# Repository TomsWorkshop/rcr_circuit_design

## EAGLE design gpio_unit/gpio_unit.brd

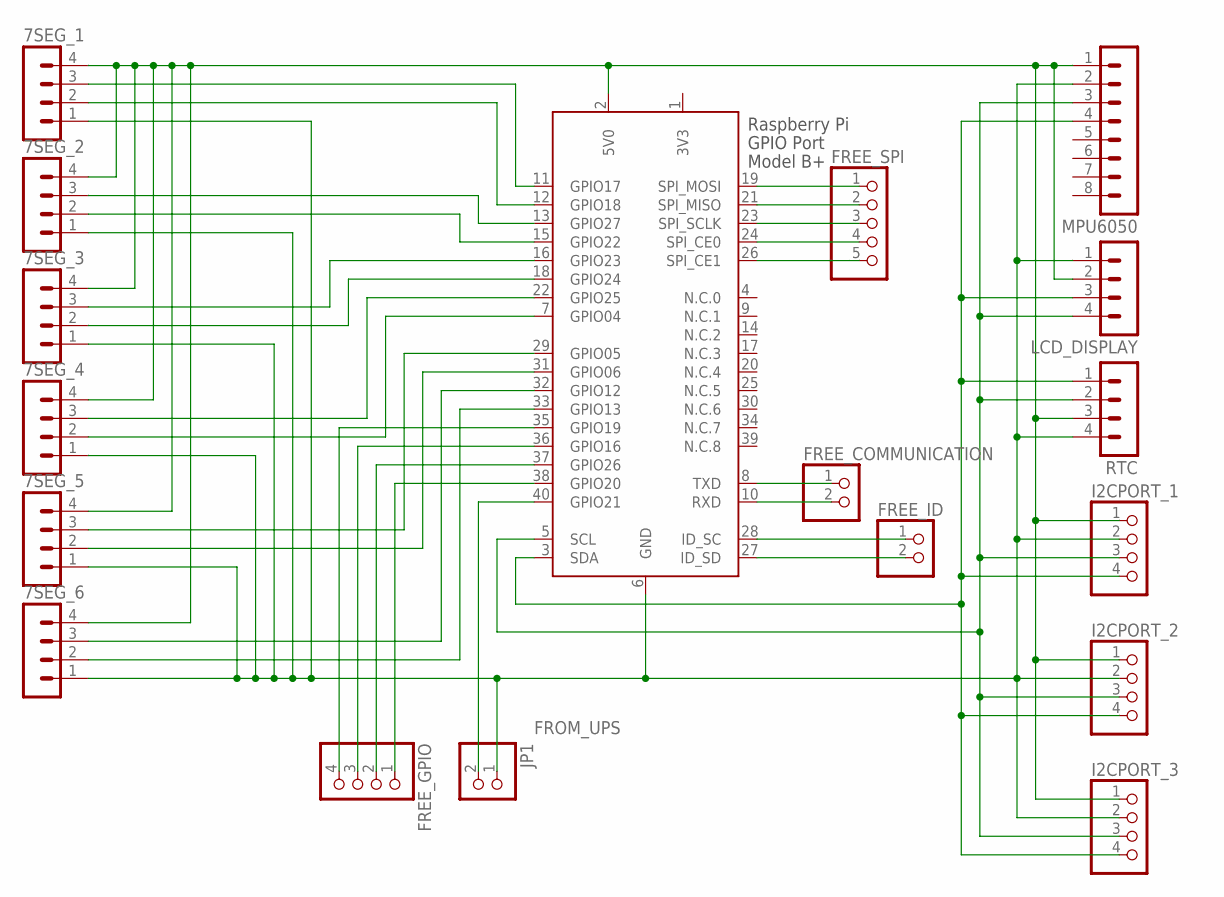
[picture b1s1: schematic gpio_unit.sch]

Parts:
7SEG_1, 7SEG_2, 7SEG_3, 7SEG_4, 7SEG_5, 7SEG_6: MA04-1
FREE_COMMUNICATION: PINHD-1X2/90; 1X02/90
FREE_GPIO: PINHD-1X4/90; 1X04/90
FREE_ID: PINHD-1X2/90; 1X02/90
FREE_SPI: PINHD-1X5/90; 1X05/90
I2CPORT_1, I2CPORT_2, I2CPORT_3: PINHD-1X4; 1X04
JP1: PINHD-1X2; 1X02
LCD_DISPLAY: MA04-1
MPU6050: MA08-1
RTC: MA04-1
X1: RASPI_GPIO_B+_PIN

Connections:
3V3: X1.1 (3V3)
FROM_UPS: JP1.2, X1.40 (GPIO21)
unnamed: 7SEG_1.1, 7SEG_2.1, 7SEG_3.1, 7SEG_4.1, 7SEG_5.1, 7SEG_6.1, I2CPORT_1.2, I2CPORT_2.2, I2CPORT_3.2, JP1.1, LCD_DISPLAY.1, MPU6050.2, RTC.4, X1.6 (GND)
unnamed: 7SEG_1.3, X1.11 (GPIO17)
unnamed: 7SEG_1.2, X1.12 (GPIO18)
unnamed: 7SEG_2.3, X1.13 (GPIO27)
unnamed: I2CPORT_1.3, I2CPORT_2.3, I2CPORT_3.3, LCD_DISPLAY.4, MPU6050.3, RTC.2, X1.5 (SCL)
unnamed: 7SEG_2.2, X1.15 (GPIO22)
unnamed: 7SEG_3.3, X1.16 (GPIO23)
unnamed: 7SEG_3.2, X1.18 (GPIO24)
unnamed: 7SEG_4.3, X1.22 (GPIO25)
unnamed: 7SEG_4.2, X1.7 (GPIO04)
unnamed: 7SEG_5.3, X1.29 (GPIO05)
unnamed: 7SEG_5.2, X1.31 (GPIO06)
unnamed: 7SEG_6.3, X1.32 (GPIO12)
unnamed: 7SEG_6.2, X1.33 (GPIO13)
unnamed: I2CPORT_1.4, I2CPORT_2.4, I2CPORT_3.4, LCD_DISPLAY.3, MPU6050.4, RTC.1, X1.3 (SDA)
unnamed: FREE_SPI.1, X1.19 (SPI_MOSI)
unnamed: FREE_SPI.2, X1.21 (SPI_MISO)
unnamed: FREE_SPI.3, X1.23 (SPI_SCLK)
unnamed: FREE_SPI.4, X1.24 (SPI_CE0)
unnamed: FREE_SPI.5, X1.26 (SPI_CE1)
unnamed: FREE_COMMUNICATION.1, X1.8 (TXD)
unnamed: FREE_COMMUNICATION.2, X1.10 (RXD)
unnamed: FREE_ID.1, X1.28 (ID_SC)
unnamed: FREE_ID.2, X1.27 (ID_SD)
unnamed: FREE_GPIO.4, X1.35 (GPIO19)
unnamed: FREE_GPIO.3, X1.36 (GPIO16)
unnamed: FREE_GPIO.2, X1.37 (GPIO26)
unnamed: FREE_GPIO.1, X1.38 (GPIO20)
VDD: 7SEG_1.4, 7SEG_2.4, 7SEG_3.4, 7SEG_4.4, 7SEG_5.4, 7SEG_6.4, I2CPORT_1.1, I2CPORT_2.1, I2CPORT_3.1, LCD_DISPLAY.2, MPU6050.1, RTC.3, X1.2 (5V0)

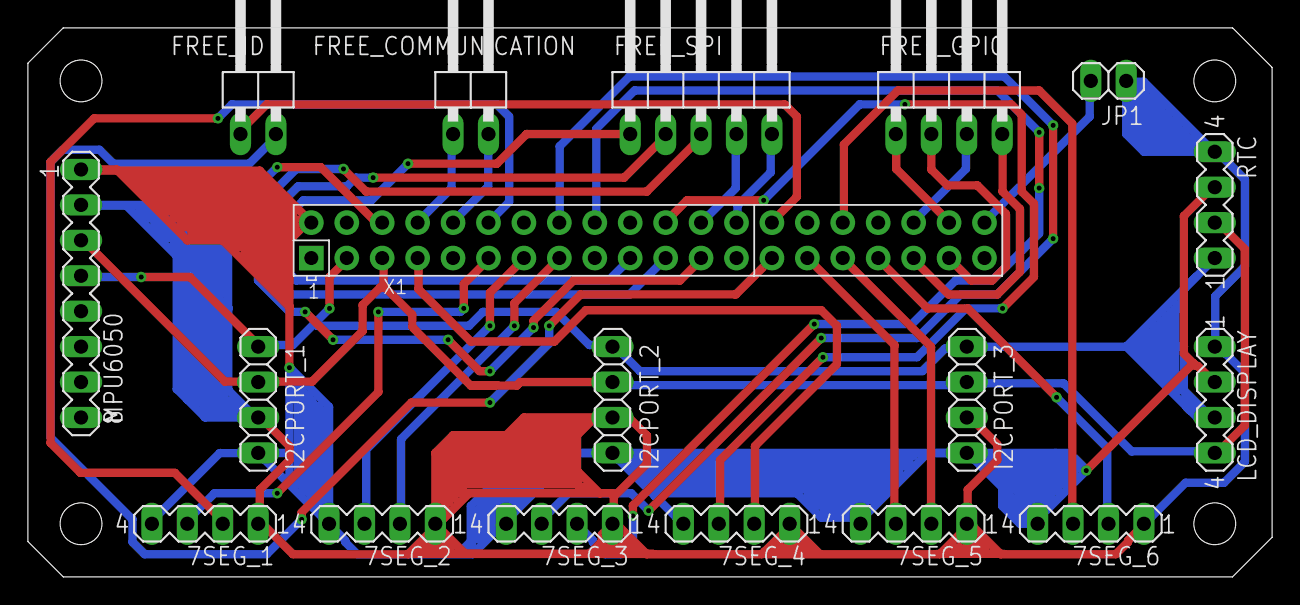
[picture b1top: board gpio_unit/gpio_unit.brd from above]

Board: 2 copper layers, 89.2 x 39.4 mm, 18 parts (0 on the bottom side), 30 nets.

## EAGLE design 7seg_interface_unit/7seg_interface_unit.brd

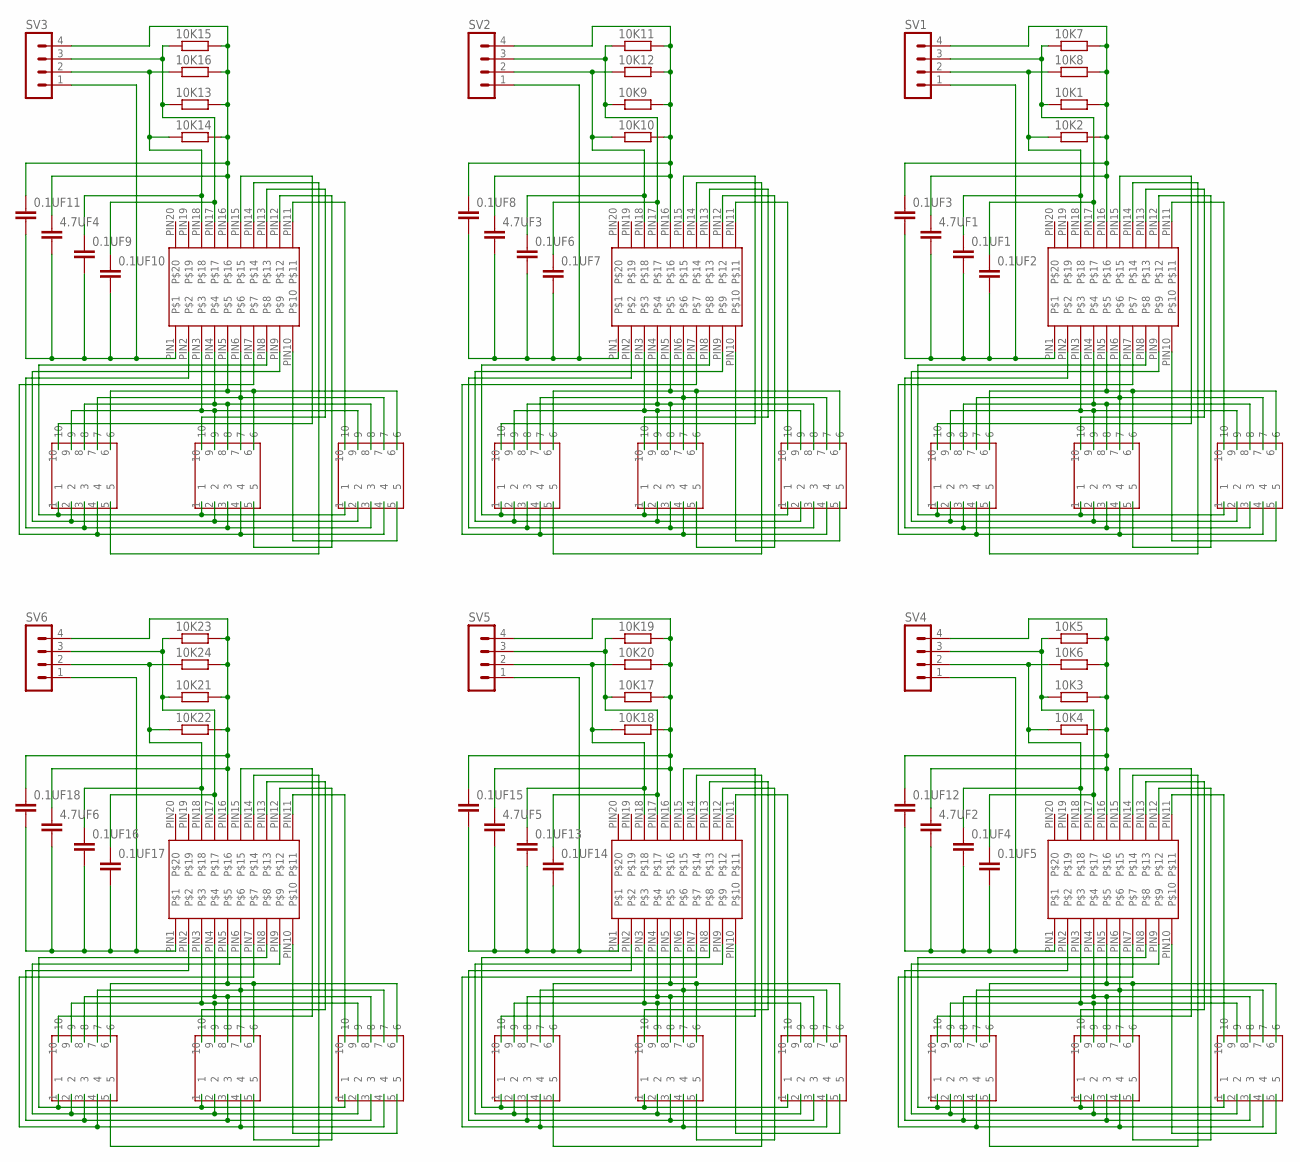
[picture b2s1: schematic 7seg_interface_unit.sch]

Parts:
0.1UF1, 0.1UF2, 0.1UF3, 0.1UF4, 0.1UF5, 0.1UF6, 0.1UF7, 0.1UF8, 0.1UF9, 0.1UF10, 0.1UF11, 0.1UF12, 0.1UF13, 0.1UF14, 0.1UF15, 0.1UF16, 0.1UF17, 0.1UF18: CC1206; C1206
4.7UF1, 4.7UF2, 4.7UF3, 4.7UF4, 4.7UF5, 4.7UF6: CC2012; C2012
10K1, 10K2, 10K3, 10K4, 10K5, 10K6, 10K7, 10K8, 10K9, 10K10, 10K11, 10K12, 10K13, 10K14, 10K15, 10K16, 10K17, 10K18, 10K19, 10K20, 10K21, 10K22, 10K23, 10K24: RR1206; R1206
LED1, LED2, LED3, LED4, LED5, LED6, LED7, LED8, LED9, LED10, LED11, LED12, LED13, LED14, LED15, LED16, LED17, LED18: 7SEG
SV1, SV2, SV3, SV4, SV5, SV6: MA04-1
TM1637-SMD1, TM1637-SMD2, TM1637-SMD3, TM1637-SMD4, TM1637-SMD5, TM1637-SMD6: TM1637

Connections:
unnamed: LED1.1, LED2.1, LED3.1, TM1637-SMD1.PIN8
unnamed: LED1.2, LED2.2, LED3.2, TM1637-SMD1.PIN9
unnamed: LED1.3, LED2.3, LED3.3, TM1637-SMD1.PIN2
unnamed: LED10.1, LED11.1, LED12.1, TM1637-SMD4.PIN8
unnamed: LED10.2, LED11.2, LED12.2, TM1637-SMD4.PIN9
unnamed: LED1.4, LED2.4, LED3.4, TM1637-SMD1.PIN7
unnamed: LED10.3, LED11.3, LED12.3, TM1637-SMD4.PIN2
unnamed: LED1.6, LED2.6, LED3.6, TM1637-SMD1.PIN5
unnamed: LED1.7, LED2.7, LED3.7, TM1637-SMD1.PIN6
unnamed: LED10.4, LED11.4, LED12.4, TM1637-SMD4.PIN7
unnamed: LED1.8, LED2.8, LED3.8, TM1637-SMD1.PIN4
unnamed: LED1.9, LED2.9, LED3.9, TM1637-SMD1.PIN3
unnamed: LED3.5, TM1637-SMD1.PIN10
unnamed: LED3.10, TM1637-SMD1.PIN11
unnamed: LED2.5, TM1637-SMD1.PIN12
unnamed: LED2.10, TM1637-SMD1.PIN13
unnamed: LED1.5, TM1637-SMD1.PIN14
unnamed: LED1.10, TM1637-SMD1.PIN15
unnamed: 0.1UF1.1, 10K2.1, 10K8.1, SV1.2, TM1637-SMD1.PIN18
unnamed: 0.1UF2.1, 10K1.1, 10K7.1, SV1.3, TM1637-SMD1.PIN17
unnamed: 0.1UF3.1, 4.7UF1.1, 10K1.2, 10K2.2, 10K7.2, 10K8.2, SV1.4, TM1637-SMD1.PIN16
unnamed: 0.1UF1.2, 0.1UF2.2, 0.1UF3.2, 4.7UF1.2, SV1.1, TM1637-SMD1.PIN1
unnamed: LED4.1, LED5.1, LED6.1, TM1637-SMD2.PIN8
unnamed: LED4.2, LED5.2, LED6.2, TM1637-SMD2.PIN9
unnamed: LED4.3, LED5.3, LED6.3, TM1637-SMD2.PIN2
unnamed: LED4.4, LED5.4, LED6.4, TM1637-SMD2.PIN7
unnamed: LED4.6, LED5.6, LED6.6, TM1637-SMD2.PIN5
unnamed: LED4.7, LED5.7, LED6.7, TM1637-SMD2.PIN6
unnamed: LED4.8, LED5.8, LED6.8, TM1637-SMD2.PIN4
unnamed: LED4.9, LED5.9, LED6.9, TM1637-SMD2.PIN3
unnamed: LED5.5, TM1637-SMD2.PIN10
unnamed: LED5.10, TM1637-SMD2.PIN11
unnamed: LED4.5, TM1637-SMD2.PIN12
unnamed: LED10.6, LED11.6, LED12.6, TM1637-SMD4.PIN5
unnamed: LED4.10, TM1637-SMD2.PIN13
unnamed: LED6.5, TM1637-SMD2.PIN14
unnamed: LED6.10, TM1637-SMD2.PIN15
unnamed: 0.1UF6.1, 10K10.1, 10K12.1, SV2.2, TM1637-SMD2.PIN18
unnamed: 0.1UF7.1, 10K9.1, 10K11.1, SV2.3, TM1637-SMD2.PIN17
unnamed: 0.1UF8.1, 4.7UF3.1, 10K9.2, 10K10.2, 10K11.2, 10K12.2, SV2.4, TM1637-SMD2.PIN16
unnamed: 0.1UF6.2, 0.1UF7.2, 0.1UF8.2, 4.7UF3.2, SV2.1, TM1637-SMD2.PIN1
unnamed: LED7.1, LED8.1, LED9.1, TM1637-SMD3.PIN8
unnamed: LED7.2, LED8.2, LED9.2, TM1637-SMD3.PIN9
unnamed: LED10.7, LED11.7, LED12.7, TM1637-SMD4.PIN6
unnamed: LED7.3, LED8.3, LED9.3, TM1637-SMD3.PIN2
unnamed: LED7.4, LED8.4, LED9.4, TM1637-SMD3.PIN7
unnamed: LED7.6, LED8.6, LED9.6, TM1637-SMD3.PIN5
unnamed: LED7.7, LED8.7, LED9.7, TM1637-SMD3.PIN6
unnamed: LED7.8, LED8.8, LED9.8, TM1637-SMD3.PIN4
unnamed: LED7.9, LED8.9, LED9.9, TM1637-SMD3.PIN3
unnamed: LED8.5, TM1637-SMD3.PIN10
unnamed: LED8.10, TM1637-SMD3.PIN11
unnamed: LED7.5, TM1637-SMD3.PIN12
unnamed: LED7.10, TM1637-SMD3.PIN13
unnamed: LED9.5, TM1637-SMD3.PIN14
unnamed: LED9.10, TM1637-SMD3.PIN15
unnamed: 0.1UF9.1, 10K14.1, 10K16.1, SV3.2, TM1637-SMD3.PIN18
unnamed: 0.1UF10.1, 10K13.1, 10K15.1, SV3.3, TM1637-SMD3.PIN17
unnamed: 0.1UF11.1, 4.7UF4.1, 10K13.2, 10K14.2, 10K15.2, 10K16.2, SV3.4, TM1637-SMD3.PIN16
unnamed: 0.1UF9.2, 0.1UF10.2, 0.1UF11.2, 4.7UF4.2, SV3.1, TM1637-SMD3.PIN1
unnamed: LED10.8, LED11.8, LED12.8, TM1637-SMD4.PIN4
unnamed: LED10.9, LED11.9, LED12.9, TM1637-SMD4.PIN3
unnamed: LED11.5, TM1637-SMD4.PIN10
unnamed: LED11.10, TM1637-SMD4.PIN11
unnamed: LED10.5, TM1637-SMD4.PIN12
unnamed: LED10.10, TM1637-SMD4.PIN13
unnamed: LED12.5, TM1637-SMD4.PIN14
unnamed: LED12.10, TM1637-SMD4.PIN15
unnamed: 0.1UF4.1, 10K4.1, 10K6.1, SV4.2, TM1637-SMD4.PIN18
unnamed: 0.1UF5.1, 10K3.1, 10K5.1, SV4.3, TM1637-SMD4.PIN17
unnamed: 0.1UF12.1, 4.7UF2.1, 10K3.2, 10K4.2, 10K5.2, 10K6.2, SV4.4, TM1637-SMD4.PIN16
unnamed: 0.1UF4.2, 0.1UF5.2, 0.1UF12.2, 4.7UF2.2, SV4.1, TM1637-SMD4.PIN1
unnamed: LED13.1, LED14.1, LED15.1, TM1637-SMD5.PIN8
unnamed: LED13.2, LED14.2, LED15.2, TM1637-SMD5.PIN9
unnamed: LED13.3, LED14.3, LED15.3, TM1637-SMD5.PIN2
unnamed: LED13.4, LED14.4, LED15.4, TM1637-SMD5.PIN7
unnamed: LED13.6, LED14.6, LED15.6, TM1637-SMD5.PIN5
unnamed: LED13.7, LED14.7, LED15.7, TM1637-SMD5.PIN6
unnamed: LED13.8, LED14.8, LED15.8, TM1637-SMD5.PIN4
unnamed: LED13.9, LED14.9, LED15.9, TM1637-SMD5.PIN3
unnamed: LED14.5, TM1637-SMD5.PIN10
unnamed: LED14.10, TM1637-SMD5.PIN11
unnamed: LED13.5, TM1637-SMD5.PIN12
unnamed: LED13.10, TM1637-SMD5.PIN13
unnamed: LED15.5, TM1637-SMD5.PIN14
unnamed: LED15.10, TM1637-SMD5.PIN15
unnamed: 0.1UF13.1, 10K18.1, 10K20.1, SV5.2, TM1637-SMD5.PIN18
unnamed: 0.1UF14.1, 10K17.1, 10K19.1, SV5.3, TM1637-SMD5.PIN17
unnamed: 0.1UF15.1, 4.7UF5.1, 10K17.2, 10K18.2, 10K19.2, 10K20.2, SV5.4, TM1637-SMD5.PIN16
unnamed: 0.1UF13.2, 0.1UF14.2, 0.1UF15.2, 4.7UF5.2, SV5.1, TM1637-SMD5.PIN1
unnamed: LED16.1, LED17.1, LED18.1, TM1637-SMD6.PIN8
unnamed: LED16.2, LED17.2, LED18.2, TM1637-SMD6.PIN9
unnamed: LED16.3, LED17.3, LED18.3, TM1637-SMD6.PIN2
unnamed: LED16.4, LED17.4, LED18.4, TM1637-SMD6.PIN7
unnamed: LED16.6, LED17.6, LED18.6, TM1637-SMD6.PIN5
unnamed: LED16.7, LED17.7, LED18.7, TM1637-SMD6.PIN6
unnamed: LED16.8, LED17.8, LED18.8, TM1637-SMD6.PIN4
unnamed: LED16.9, LED17.9, LED18.9, TM1637-SMD6.PIN3
unnamed: LED17.5, TM1637-SMD6.PIN10
unnamed: LED17.10, TM1637-SMD6.PIN11
unnamed: LED16.5, TM1637-SMD6.PIN12
unnamed: LED16.10, TM1637-SMD6.PIN13
unnamed: LED18.5, TM1637-SMD6.PIN14
unnamed: LED18.10, TM1637-SMD6.PIN15
unnamed: 0.1UF16.1, 10K22.1, 10K24.1, SV6.2, TM1637-SMD6.PIN18
unnamed: 0.1UF17.1, 10K21.1, 10K23.1, SV6.3, TM1637-SMD6.PIN17
unnamed: 0.1UF18.1, 4.7UF6.1, 10K21.2, 10K22.2, 10K23.2, 10K24.2, SV6.4, TM1637-SMD6.PIN16
unnamed: 0.1UF16.2, 0.1UF17.2, 0.1UF18.2, 4.7UF6.2, SV6.1, TM1637-SMD6.PIN1

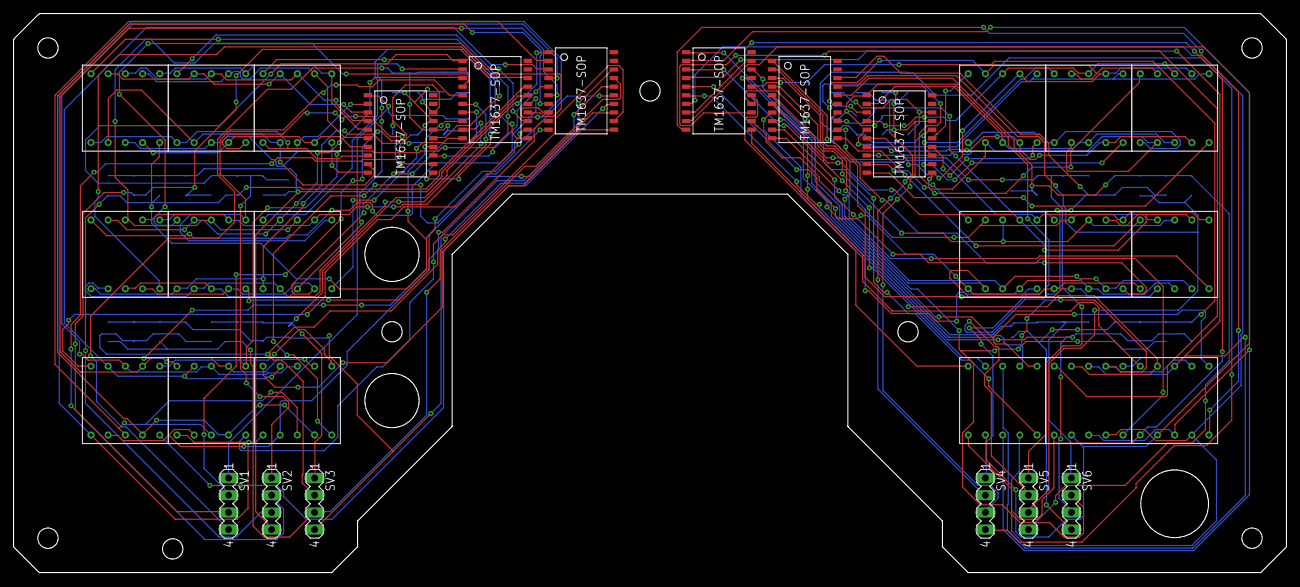
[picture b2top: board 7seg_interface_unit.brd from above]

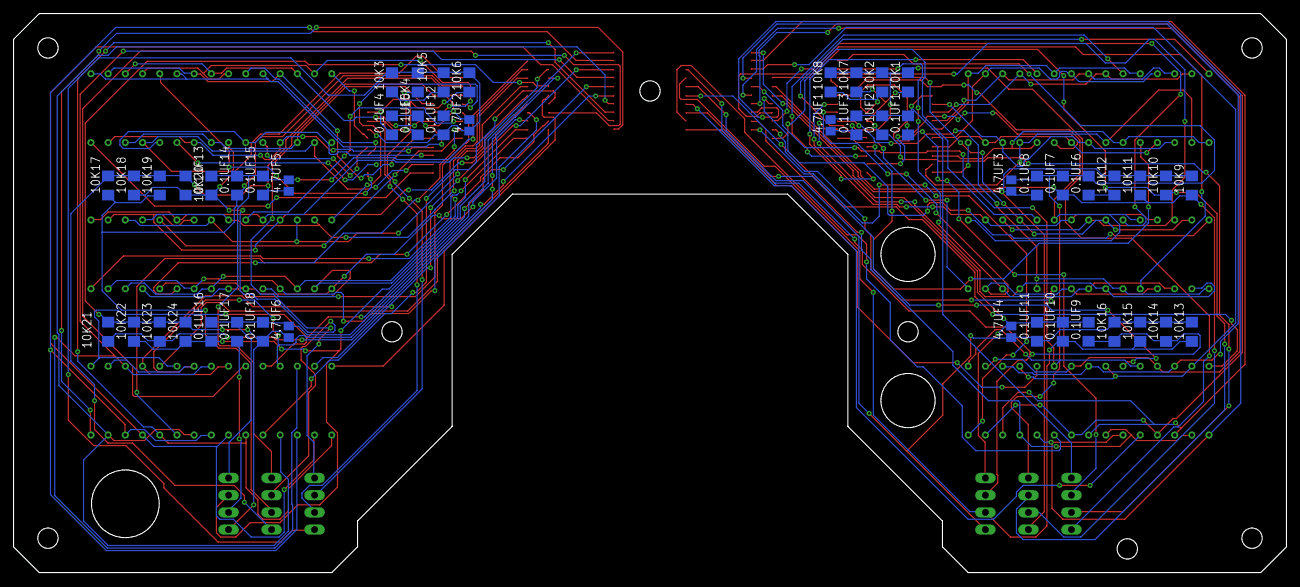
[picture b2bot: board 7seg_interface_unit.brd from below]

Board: 2 copper layers, 187.8 x 82.5 mm, 78 parts (48 on the bottom side), 108 nets.

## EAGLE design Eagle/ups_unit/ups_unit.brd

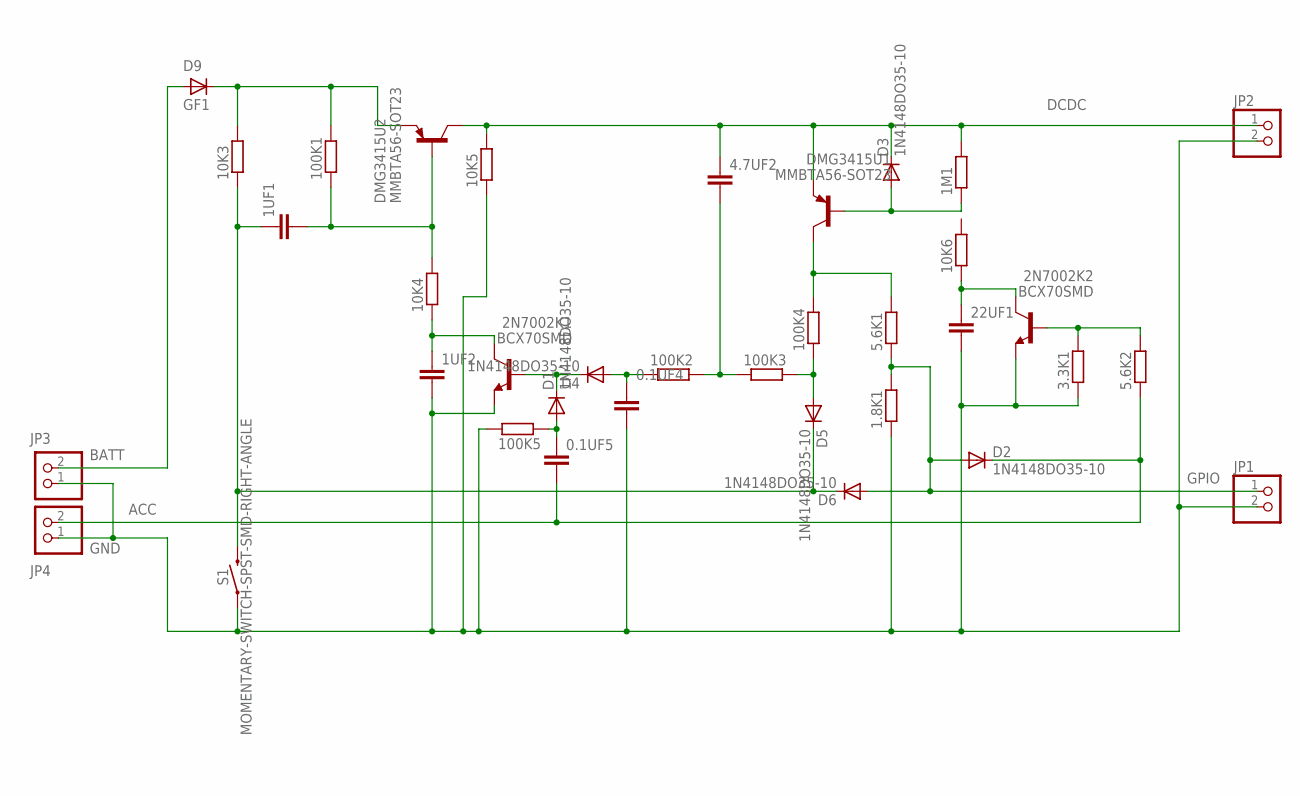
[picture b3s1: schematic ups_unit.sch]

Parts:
0.1UF4, 0.1UF5: CC1206; C1206
1.8K1, 1M1, 3.3K1, 5.6K1, 5.6K2, 10K3, 10K4, 10K5, 10K6, 100K1, 100K2, 100K3, 100K4, 100K5: RR1206; R1206
1UF1, 1UF2: CC0603; C0603
2N7002K1, 2N7002K2: BCX70SMD; SOT23
4.7UF2: CC2012; C2012
22UF1: C; C0805
D1, D2, D3, D4, D5, D6: 1N4148DO35-10; DO35-10
D9: GF1; SMA-DO214AC
DMG3415U1, DMG3415U2: MMBTA56-SOT23; SOT23
JP1, JP2, JP3, JP4: PINHD-1X2; 1X02
S1: MOMENTARY-SWITCH-SPST-SMD-RIGHT-ANGLE; TACTILE_SWITCH_SMD_RIGHT_ANGLE

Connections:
ACC: 0.1UF5.2, 5.6K2.1, D2.C, JP4.2
BATT: D9.A, JP3.2
DCDC: 1M1.2, 4.7UF2.1, 10K5.2, D3.C, DMG3415U1.2 (E), DMG3415U2.3 (C), JP2.1
GND: 0.1UF4.2, 1.8K1.1, 1UF2.2, 2N7002K1.2 (E), 2N7002K2.2 (E), 3.3K1.1, 10K5.1, 22UF1.2, 100K5.2, JP1.2, JP2.2, JP3.1, JP4.1, S1.1
GPIO: 1.8K1.2, 5.6K1.1, D2.A, D6.A, JP1.1
unnamed: 10K3.2, 100K1.2, D9.K (C), DMG3415U2.2 (E)
unnamed: 1UF1.1, 10K3.1, D5.C, D6.C, S1.2
unnamed: 1UF1.2, 10K4.2, 100K1.1, DMG3415U2.1 (B)
unnamed: 1UF2.1, 2N7002K1.3 (C), 10K4.1
unnamed: 2N7002K1.1 (B), D1.C, D4.C
unnamed: 0.1UF4.1, 100K2.1, D4.A
unnamed: 4.7UF2.2, 100K2.2, 100K3.1
unnamed: 5.6K1.2, 100K4.2, DMG3415U1.3 (C)
unnamed: 100K3.2, 100K4.1, D5.A
unnamed: 0.1UF5.1, 100K5.1, D1.A
unnamed: 1M1.1, D3.A, DMG3415U1.1 (B)
unnamed: 2N7002K2.3 (C), 10K6.1, 22UF1.1
unnamed: 2N7002K2.1 (B), 3.3K1.2, 5.6K2.2

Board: 2 copper layers, 36 parts (32 on the bottom side), 18 nets, no tracks yet.

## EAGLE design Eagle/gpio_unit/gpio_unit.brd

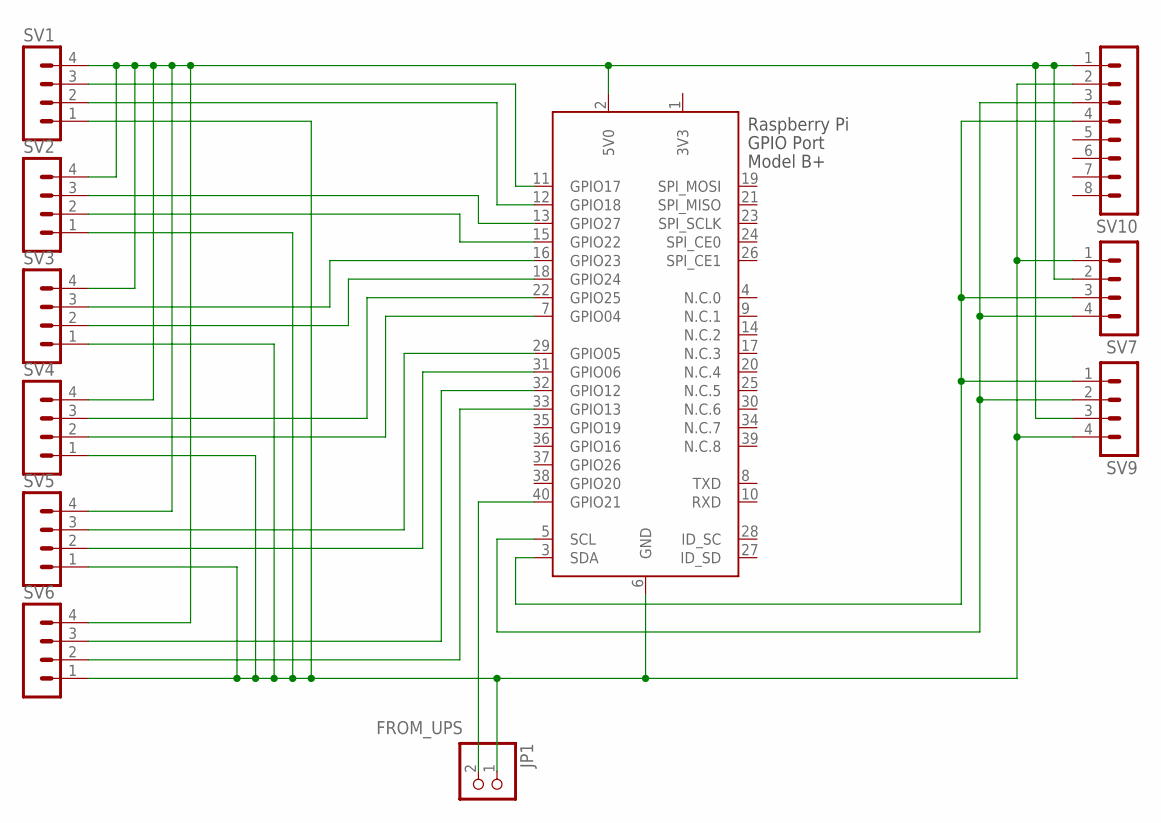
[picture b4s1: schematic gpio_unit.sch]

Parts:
JP1: PINHD-1X2; 1X02
SV1, SV2, SV3, SV4, SV5, SV6, SV7, SV9: MA04-1
SV10: MA08-1
X1: RASPI_GPIO_B+_PIN

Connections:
3V3: X1.1 (3V3)
FROM_UPS: JP1.2, X1.40 (GPIO21)
unnamed: JP1.1, SV1.1, SV2.1, SV3.1, SV4.1, SV5.1, SV6.1, SV7.1, SV9.4, SV10.2, X1.6 (GND)
unnamed: SV1.3, X1.11 (GPIO17)
unnamed: SV1.2, X1.12 (GPIO18)
unnamed: SV2.3, X1.13 (GPIO27)
unnamed: SV7.4, SV9.2, SV10.3, X1.5 (SCL)
unnamed: SV2.2, X1.15 (GPIO22)
unnamed: SV3.3, X1.16 (GPIO23)
unnamed: SV3.2, X1.18 (GPIO24)
unnamed: SV4.3, X1.22 (GPIO25)
unnamed: SV4.2, X1.7 (GPIO04)
unnamed: SV5.3, X1.29 (GPIO05)
unnamed: SV5.2, X1.31 (GPIO06)
unnamed: SV6.3, X1.32 (GPIO12)
unnamed: SV6.2, X1.33 (GPIO13)
unnamed: SV7.3, SV9.1, SV10.4, X1.3 (SDA)
VDD: SV1.4, SV2.4, SV3.4, SV4.4, SV5.4, SV6.4, SV7.2, SV9.3, SV10.1, X1.2 (5V0)

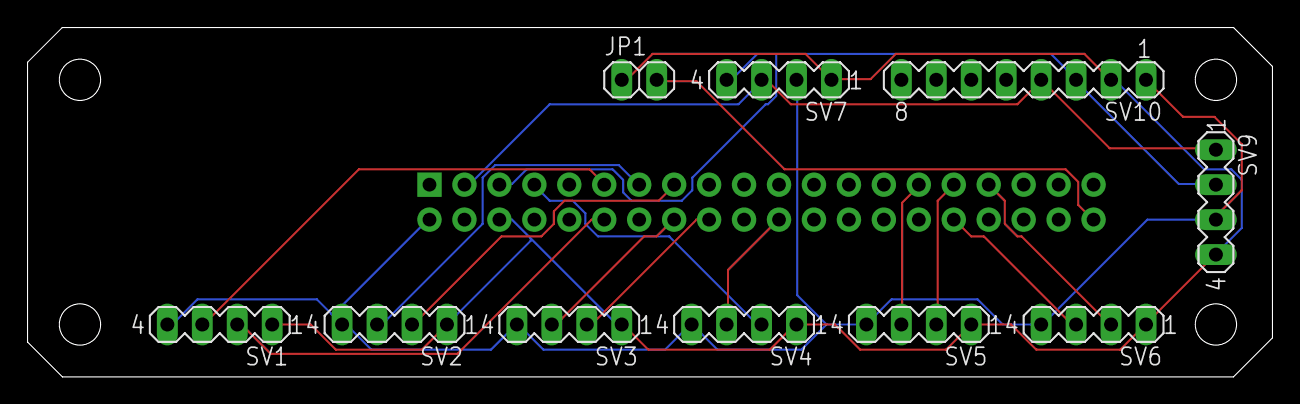
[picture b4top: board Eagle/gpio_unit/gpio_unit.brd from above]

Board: 2 copper layers, 90.5 x 25.4 mm, 11 parts (1 on the bottom side), 17 nets.

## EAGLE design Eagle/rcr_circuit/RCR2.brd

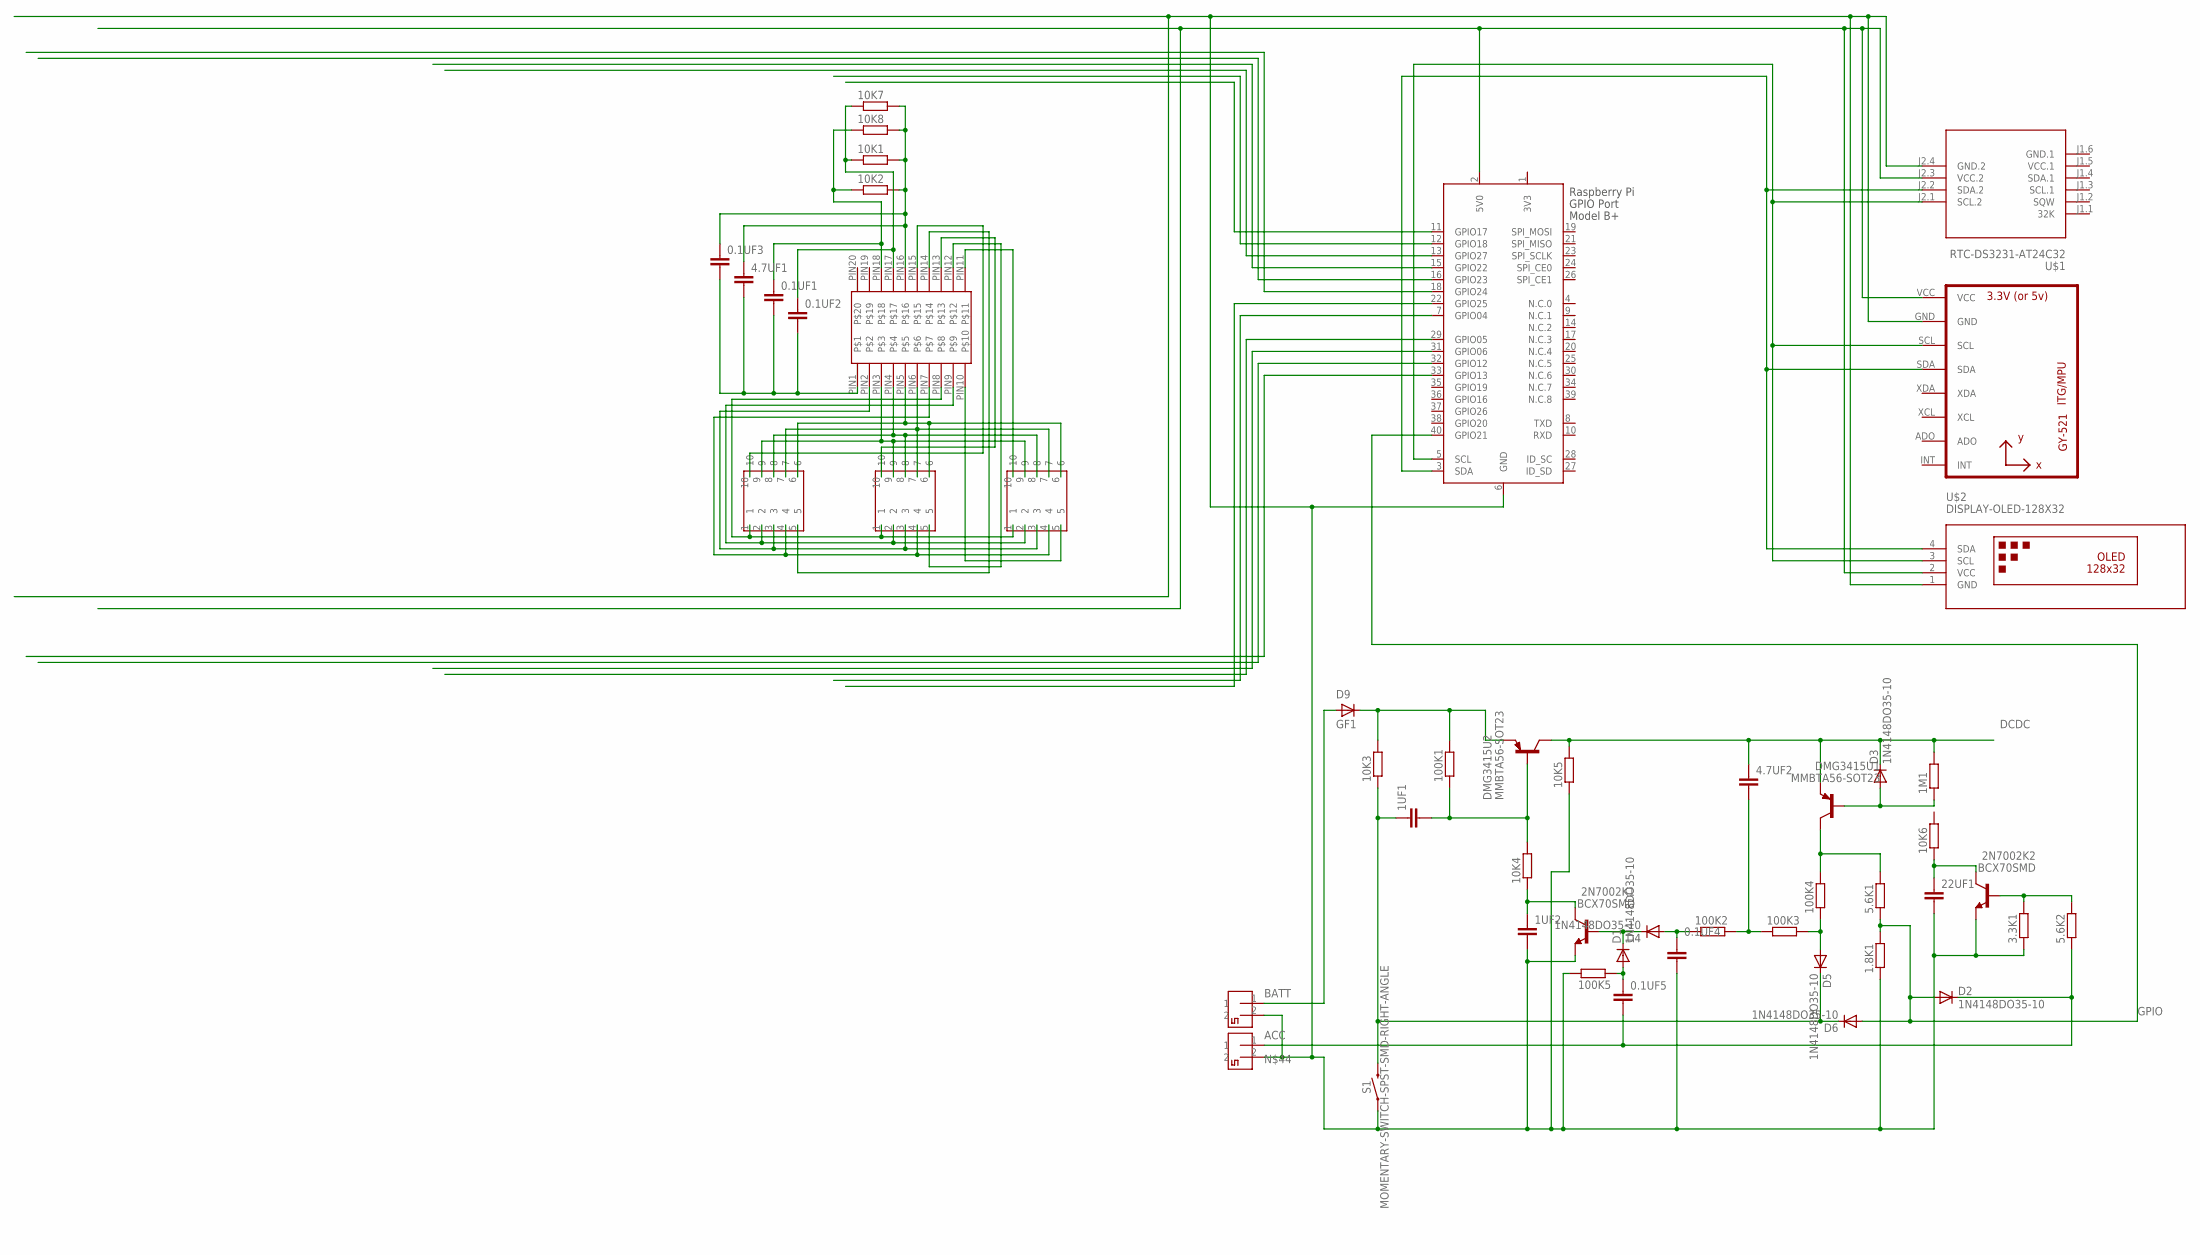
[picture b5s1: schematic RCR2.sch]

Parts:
0.1UF1, 0.1UF2, 0.1UF3, 0.1UF4, 0.1UF5: CC1206; C1206
1.8K1, 1M1, 3.3K1, 5.6K1, 5.6K2, 10K1, 10K2, 10K3, 10K4, 10K5, 10K6, 10K7, 10K8, 100K1, 100K2, 100K3, 100K4, 100K5: RR1206; R1206
1UF1, 1UF2: CC0603; C0603
2N7002K1, 2N7002K2: BCX70SMD; SOT23
4.7UF1, 4.7UF2: CC2012; C2012
22UF1: C; C0805
CONNECTOR2, CONNECTOR3: 2PIN
D1, D2, D3, D4, D5, D6: 1N4148DO35-10; DO35-10
D9: GF1; SMA-DO214AC
DMG3415U1, DMG3415U2: MMBTA56-SOT23; SOT23
LED1, LED2, LED3: 7SEG
S1: MOMENTARY-SWITCH-SPST-SMD-RIGHT-ANGLE; TACTILE_SWITCH_SMD_RIGHT_ANGLE
TM1637-SMD1: TM1637
U1: GY-521MPU6050; GY-521
U$1: RTC-DS3231-AT24C32
U$2: DISPLAY-OLED-128X32
X1: RASPI_GPIO_B+_PIN

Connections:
3V3: X1.1 (3V3)
ACC: 0.1UF5.2, 5.6K2.1, CONNECTOR2.1, D2.C
BATT: CONNECTOR3.1, D9.A
DCDC: 1M1.2, 4.7UF2.1, 10K5.2, D3.C, DMG3415U1.2 (E), DMG3415U2.3 (C)
GND.1: U$1.J1.6 (GND.1)
GPIO: 1.8K1.2, 5.6K1.1, D2.A, D6.A, X1.40 (GPIO21)
unnamed: LED1.1, LED2.1, LED3.1, TM1637-SMD1.PIN8
unnamed: LED1.2, LED2.2, LED3.2, TM1637-SMD1.PIN9
unnamed: LED1.3, LED2.3, LED3.3, TM1637-SMD1.PIN2
unnamed: LED1.4, LED2.4, LED3.4, TM1637-SMD1.PIN7
unnamed: LED1.6, LED2.6, LED3.6, TM1637-SMD1.PIN5
unnamed: LED1.7, LED2.7, LED3.7, TM1637-SMD1.PIN6
unnamed: LED1.8, LED2.8, LED3.8, TM1637-SMD1.PIN4
unnamed: LED1.9, LED2.9, LED3.9, TM1637-SMD1.PIN3
unnamed: LED3.5, TM1637-SMD1.PIN10
unnamed: LED3.10, TM1637-SMD1.PIN11
unnamed: LED2.5, TM1637-SMD1.PIN12
unnamed: LED2.10, TM1637-SMD1.PIN13
unnamed: LED1.5, TM1637-SMD1.PIN14
unnamed: LED1.10, TM1637-SMD1.PIN15
unnamed: 0.1UF1.1, 10K2.1, 10K8.1, TM1637-SMD1.PIN18
unnamed: 0.1UF2.1, 10K1.1, 10K7.1, TM1637-SMD1.PIN17
unnamed: 0.1UF3.1, 4.7UF1.1, 10K1.2, 10K2.2, 10K7.2, 10K8.2, TM1637-SMD1.PIN16
unnamed: 0.1UF1.2, 0.1UF2.2, 0.1UF3.2, 4.7UF1.2, TM1637-SMD1.PIN1
unnamed: U1.SCL, U$1.J2.1 (SCL.2), U$2.3 (SCL), X1.5 (SCL)
unnamed: 0.1UF4.2, 1.8K1.1, 1UF2.2, 2N7002K1.2 (E), 2N7002K2.2 (E), 3.3K1.1, 10K5.1, 22UF1.2, 100K5.2, CONNECTOR2.2, CONNECTOR3.2, S1.1, U1.GND, U$1.J2.4 (GND.2), U$2.1 (GND), X1.6 (GND)
unnamed: U1.SDA, U$1.J2.2 (SDA.2), U$2.4 (SDA), X1.3 (SDA)
unnamed: 10K3.2, 100K1.2, D9.K (C), DMG3415U2.2 (E)
unnamed: 1UF1.1, 10K3.1, D5.C, D6.C, S1.2
unnamed: 1UF1.2, 10K4.2, 100K1.1, DMG3415U2.1 (B)
unnamed: 1UF2.1, 2N7002K1.3 (C), 10K4.1
unnamed: 2N7002K1.1 (B), D1.C, D4.C
unnamed: 0.1UF4.1, 100K2.1, D4.A
unnamed: 4.7UF2.2, 100K2.2, 100K3.1
unnamed: 5.6K1.2, 100K4.2, DMG3415U1.3 (C)
unnamed: 100K3.2, 100K4.1, D5.A
unnamed: 0.1UF5.1, 100K5.1, D1.A
unnamed: 1M1.1, D3.A, DMG3415U1.1 (B)
unnamed: 2N7002K2.3 (C), 10K6.1, 22UF1.1
unnamed: 2N7002K2.1 (B), 3.3K1.2, 5.6K2.2
VCC.1: U$1.J1.5 (VCC.1)
VDD: U1.VCC, U$1.J2.3 (VCC.2), U$2.2 (VCC), X1.2 (5V0)

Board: 2 copper layers, 50 parts (47 on the bottom side), 39 nets, no tracks yet.

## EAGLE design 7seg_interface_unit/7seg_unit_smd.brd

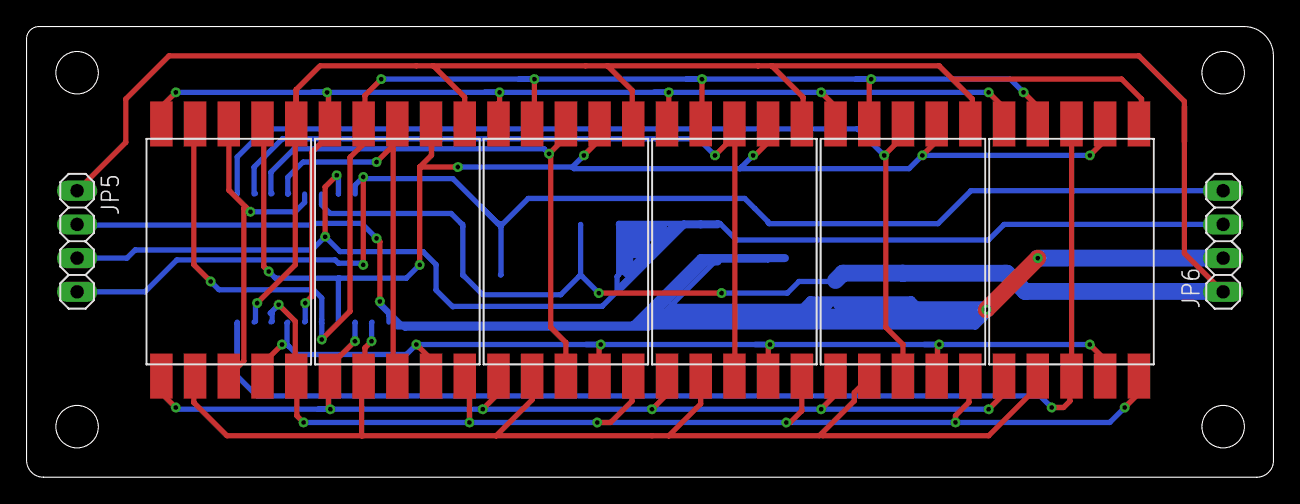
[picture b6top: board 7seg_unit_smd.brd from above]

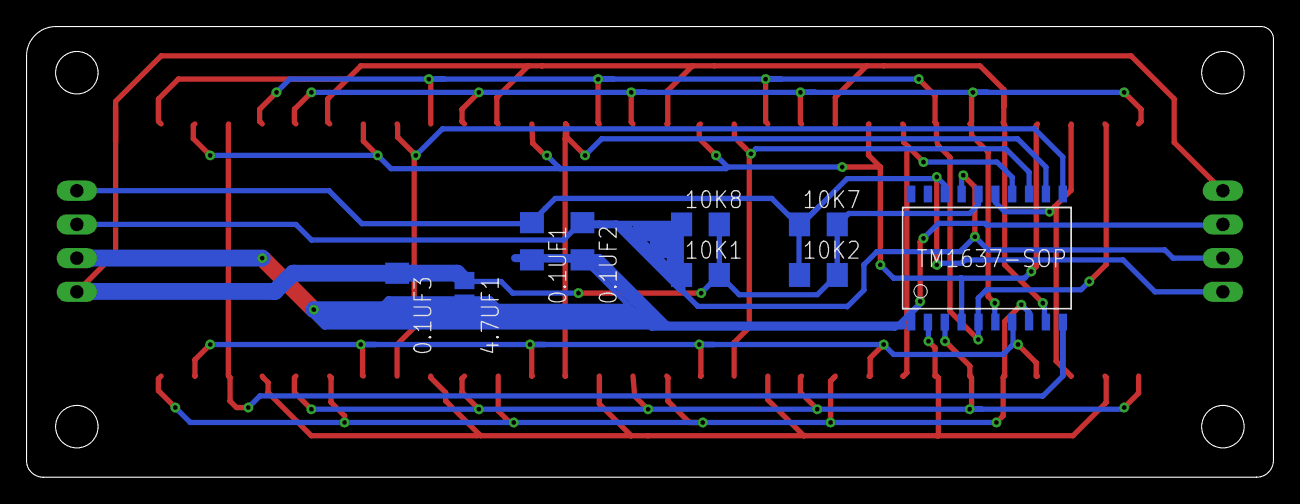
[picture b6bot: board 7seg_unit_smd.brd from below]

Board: 2 copper layers, 94.0 x 34.0 mm, 17 parts (9 on the bottom side), 18 nets.

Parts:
0.1UF1, 0.1UF2, 0.1UF3: C1206
4.7UF1: C2012
7SEG_NEW1, 7SEG_NEW2, 7SEG_NEW3, 7SEG_NEW4, 7SEG_NEW5, 7SEG_NEW6: 7SEG_NEW
10K1, 10K2, 10K7, 10K8: R1206
JP5, JP6: 1X04
TM1637-SMD1: TM1637

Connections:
CLK: 0.1UF1.1, 10K2.1, 10K7.1, JP5.4, JP6.4, TM1637-SMD1.PIN18
DIO: 0.1UF2.1, 10K1.1, 10K8.1, JP5.3, JP6.3, TM1637-SMD1.PIN17
GND: 0.1UF1.2, 0.1UF2.2, 0.1UF3.2, 4.7UF1.2, JP5.2, JP6.2, TM1637-SMD1.PIN1
unnamed: 7SEG_NEW1.P$5, 7SEG_NEW2.P$5, 7SEG_NEW3.P$5, 7SEG_NEW4.P$5, 7SEG_NEW5.P$5, 7SEG_NEW6.P$5, TM1637-SMD1.PIN9
unnamed: 7SEG_NEW6.P$3, 7SEG_NEW6.P$8, TM1637-SMD1.PIN10
unnamed: 7SEG_NEW1.P$9, 7SEG_NEW2.P$9, 7SEG_NEW3.P$9, 7SEG_NEW4.P$9, 7SEG_NEW5.P$9, 7SEG_NEW6.P$9, TM1637-SMD1.PIN7
unnamed: 7SEG_NEW5.P$3, 7SEG_NEW5.P$8, TM1637-SMD1.PIN11
unnamed: 7SEG_NEW2.P$3, 7SEG_NEW2.P$8, TM1637-SMD1.PIN12
unnamed: 7SEG_NEW1.P$3, 7SEG_NEW1.P$8, TM1637-SMD1.PIN13
unnamed: 7SEG_NEW4.P$3, 7SEG_NEW4.P$8, TM1637-SMD1.PIN14
unnamed: 7SEG_NEW3.P$3, 7SEG_NEW3.P$8, TM1637-SMD1.PIN15
unnamed: 7SEG_NEW1.P$10, 7SEG_NEW2.P$10, 7SEG_NEW3.P$10, 7SEG_NEW4.P$10, 7SEG_NEW5.P$10, 7SEG_NEW6.P$10, TM1637-SMD1.PIN8
unnamed: 7SEG_NEW1.P$1, 7SEG_NEW2.P$1, 7SEG_NEW3.P$1, 7SEG_NEW4.P$1, 7SEG_NEW5.P$1, 7SEG_NEW6.P$1, TM1637-SMD1.PIN6
unnamed: 7SEG_NEW1.P$2, 7SEG_NEW2.P$2, 7SEG_NEW3.P$2, 7SEG_NEW4.P$2, 7SEG_NEW5.P$2, 7SEG_NEW6.P$2, TM1637-SMD1.PIN5
unnamed: 7SEG_NEW1.P$4, 7SEG_NEW2.P$4, 7SEG_NEW3.P$4, 7SEG_NEW4.P$4, 7SEG_NEW5.P$4, 7SEG_NEW6.P$4, TM1637-SMD1.PIN4
unnamed: 7SEG_NEW1.P$6, 7SEG_NEW2.P$6, 7SEG_NEW3.P$6, 7SEG_NEW4.P$6, 7SEG_NEW5.P$6, 7SEG_NEW6.P$6, TM1637-SMD1.PIN3
unnamed: 7SEG_NEW1.P$7, 7SEG_NEW2.P$7, 7SEG_NEW3.P$7, 7SEG_NEW4.P$7, 7SEG_NEW5.P$7, 7SEG_NEW6.P$7, TM1637-SMD1.PIN2
VDD: 0.1UF3.1, 4.7UF1.1, 10K1.2, 10K2.2, 10K7.2, 10K8.2, JP5.1, JP6.1, TM1637-SMD1.PIN16

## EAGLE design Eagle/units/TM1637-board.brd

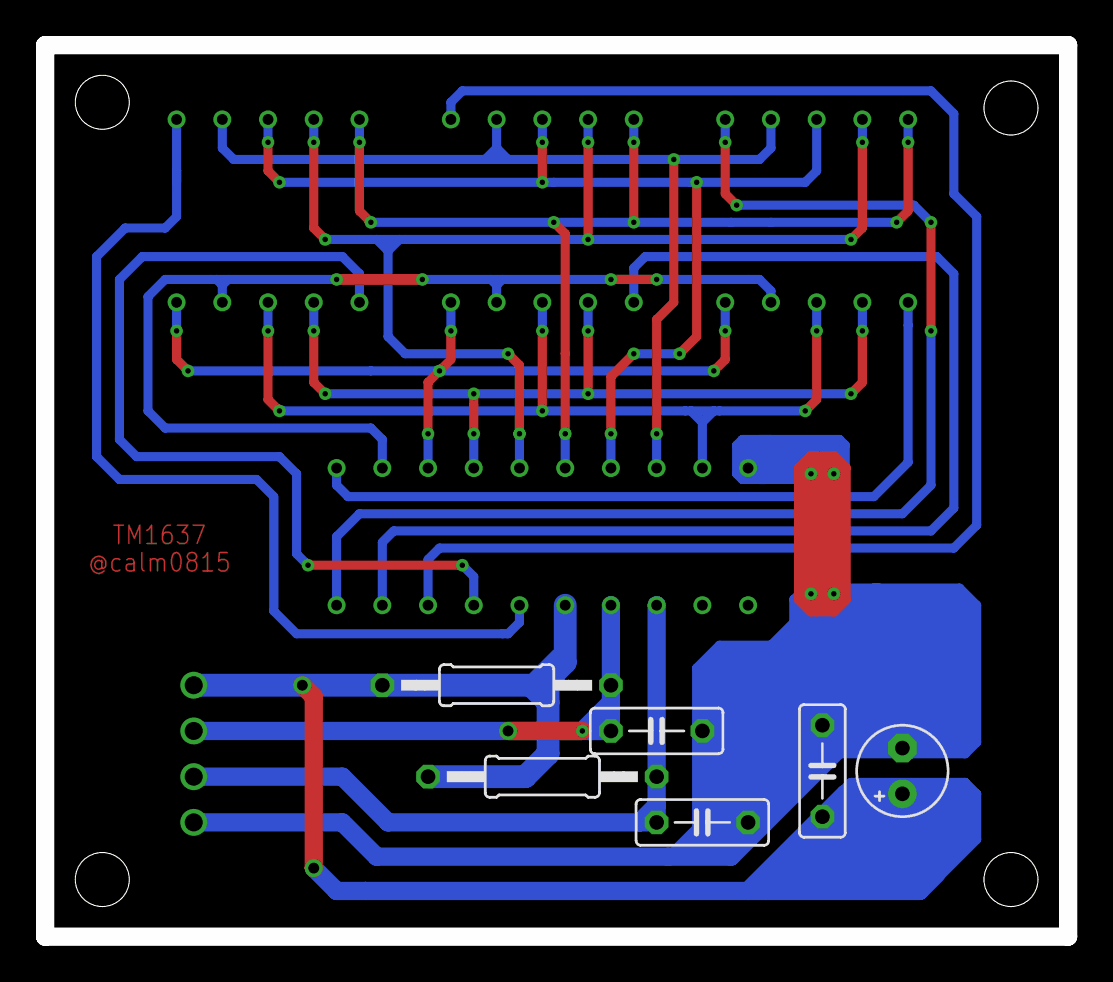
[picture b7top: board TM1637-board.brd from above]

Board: 2 copper layers, 56.8 x 49.5 mm, 6 parts (0 on the bottom side), 3 nets.

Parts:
E$1, E$3: 0207/12
E$4, E$6, E$7: C050-025X075
E$5: E2,5-5

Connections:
S$15: E$4.2, E$5.+
S$21: E$1.2, E$3.2
S$66: E$5.-, E$6.1, E$7.1

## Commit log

2020-02-02 move
2020-02-02 add new fioles
2020-02-02 making main board
2020-02-03 finish autorouter
2020-02-03 minor change
2020-02-03 description png
2020-02-03 add gpio_unit
2020-02-03 add ups_unit
2020-02-11 RPi UPS unit
2020-02-11 RPi GPIO unit
2020-02-11 autorouted board
2020-02-11 add 'seg smd library
2020-02-11 7 segment LED unit
2020-02-11 add parts list
2020-02-11 move & renamed
2020-02-11 move directory
2020-02-12 arrange comment

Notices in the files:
parts and their libraries:
diy-modules: Released under the Creative Commons Attribution 4.0 International License: http://creativecommons.org/licenses/by/4.0
SparkFun-Switches: Licensing: Creative Commons ShareAlike 4.0 International - https://creativecommons.org/licenses/by-sa/4.0
